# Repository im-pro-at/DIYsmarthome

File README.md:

# DIYsmarthome
Cheap DIY smart home system

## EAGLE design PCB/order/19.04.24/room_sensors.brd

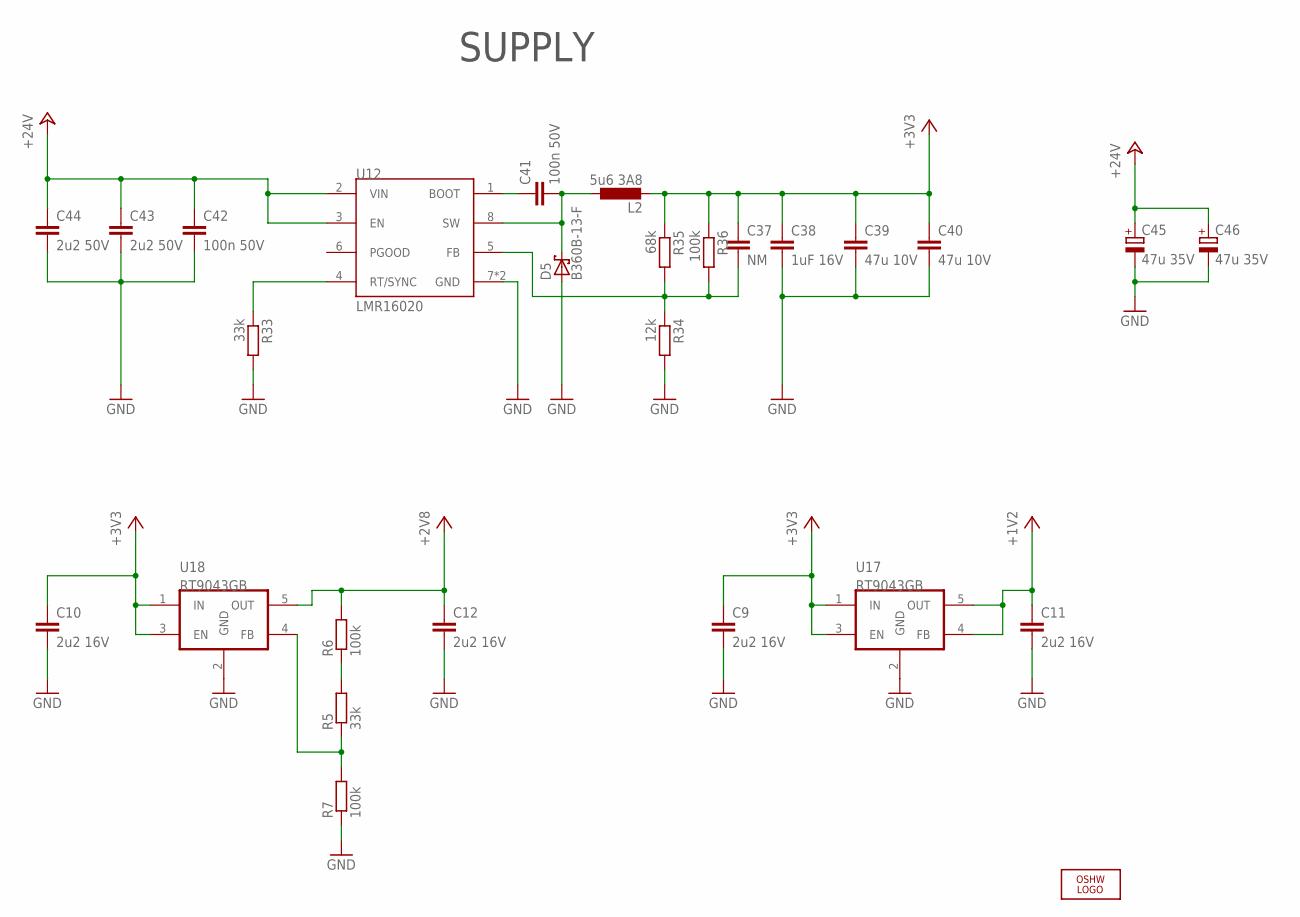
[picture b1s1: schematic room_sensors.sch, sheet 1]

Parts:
C9, C10, C11, C12: 2u2 16V; C1206
C37: NM; C0805
C38: 1uF 16V; C0805
C39, C40: 47u 10V; C1210
C41, C42: 100n 50V; C1206
C43, C44: 2u2 50V; C1206
C45, C46: 47u 35V; UD-5X5,8_NICHICON
D5: B360B-13-F; SMB
L2: 5u6 3A8; SLF10145T-150M2R2-PF
LOGO1: OSHW_LOGO_FILLX0350-NT; OSHW_FILLX350_NOTEXT
R5, R33: 33k; R1206
R6, R7, R36: 100k; R1206
R34: 12k; R1206
R35: 68k; R1206
U12: LMR16020; SOIC127P600X170-8N
U17, U18: RT9043GB; SOP95P275X110-5N

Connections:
+1V2: C11.1, U17.4 (FB), U17.5 (OUT); also elsewhere on the board
+2V8: C12.1, R6.2, U18.5 (OUT); also elsewhere on the board
+3V3: C9.1, C10.1, C37.1, C38.1, C39.1, C40.1, L2.P$2 (2), R35.1, R36.1, U17.1 (IN), U17.3 (EN), U18.1 (IN), U18.3 (EN); also elsewhere on the board
+24V: C42.1, C43.1, C44.1, C45.+, C46.+, U12.2 (VIN), U12.3 (EN); also elsewhere on the board
ESP32_EN1: R5.1, R7.2, U18.4 (FB)
GND: C9.2, C10.2, C11.2, C12.2, C38.2, C39.2, C40.2, C42.2, C43.2, C44.2, C45.-, C46.-, D5.A, R7.1, R33.2, R34.2, U12.7 (GND), U12.9 (GND), U17.2 (GND), U18.2 (GND); also elsewhere on the board
unnamed: R5.2, R6.1
unnamed: R33.1, U12.4 (RT/SYNC)
unnamed: C37.2, R34.1, R35.2, R36.2, U12.5 (FB)
unnamed: C41.2, D5.C, L2.P$1 (1), U12.8 (SW)
unnamed: C41.1, U12.1 (BOOT)

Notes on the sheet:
SUPPLY

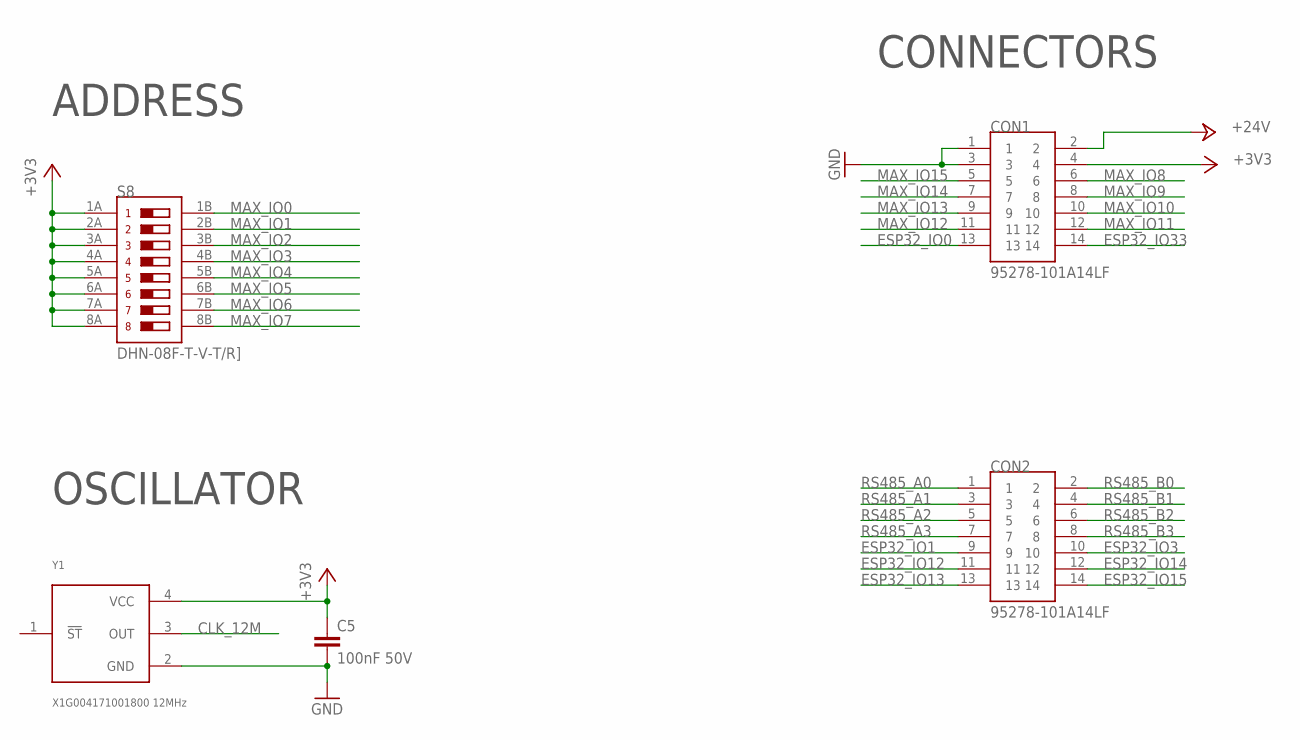
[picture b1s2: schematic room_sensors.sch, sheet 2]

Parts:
C5: 100nF 50V; C0805
CON1, CON2: 95278-101A14LF
S8: DHN-08F-T-V-T/R]
Y1: X1G004171001800 12MHz; OSCCC250X200X80-4N

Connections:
+3V3: C5.1, CON1.4, S8.1A, S8.2A, S8.3A, S8.4A, S8.5A, S8.6A, S8.7A, S8.8A, Y1.4 (VCC); also elsewhere on the board
+24V: CON1.2; also elsewhere on the board
CLK_12M: Y1.3 (OUT); also elsewhere on the board
ESP32_IO0: CON1.13; also elsewhere on the board
ESP32_IO1: CON2.9; also elsewhere on the board
ESP32_IO3: CON2.10; also elsewhere on the board
ESP32_IO12: CON2.11; also elsewhere on the board
ESP32_IO13: CON2.13; also elsewhere on the board
ESP32_IO14: CON2.12; also elsewhere on the board
ESP32_IO15: CON2.14; also elsewhere on the board
ESP32_IO33: CON1.14; also elsewhere on the board
GND: C5.2, CON1.1, CON1.3, Y1.2 (GND); also elsewhere on the board
MAX_IO0: S8.1B; also elsewhere on the board
MAX_IO1: S8.2B; also elsewhere on the board
MAX_IO2: S8.3B; also elsewhere on the board
MAX_IO3: S8.4B; also elsewhere on the board
MAX_IO4: S8.5B; also elsewhere on the board
MAX_IO5: S8.6B; also elsewhere on the board
MAX_IO6: S8.7B; also elsewhere on the board
MAX_IO7: S8.8B; also elsewhere on the board
MAX_IO8: CON1.6; also elsewhere on the board
MAX_IO9: CON1.8; also elsewhere on the board
MAX_IO10: CON1.10; also elsewhere on the board
MAX_IO11: CON1.12; also elsewhere on the board
MAX_IO12: CON1.11; also elsewhere on the board
MAX_IO13: CON1.9; also elsewhere on the board
MAX_IO14: CON1.7; also elsewhere on the board
MAX_IO15: CON1.5; also elsewhere on the board
RS485_A0: CON2.1; also elsewhere on the board
RS485_A1: CON2.3; also elsewhere on the board
RS485_A2: CON2.5; also elsewhere on the board
RS485_A3: CON2.7; also elsewhere on the board
RS485_B0: CON2.2; also elsewhere on the board
RS485_B1: CON2.4; also elsewhere on the board
RS485_B2: CON2.6; also elsewhere on the board
RS485_B3: CON2.8; also elsewhere on the board

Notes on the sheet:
CONNECTORS
ADDRESS
OSCILLATOR

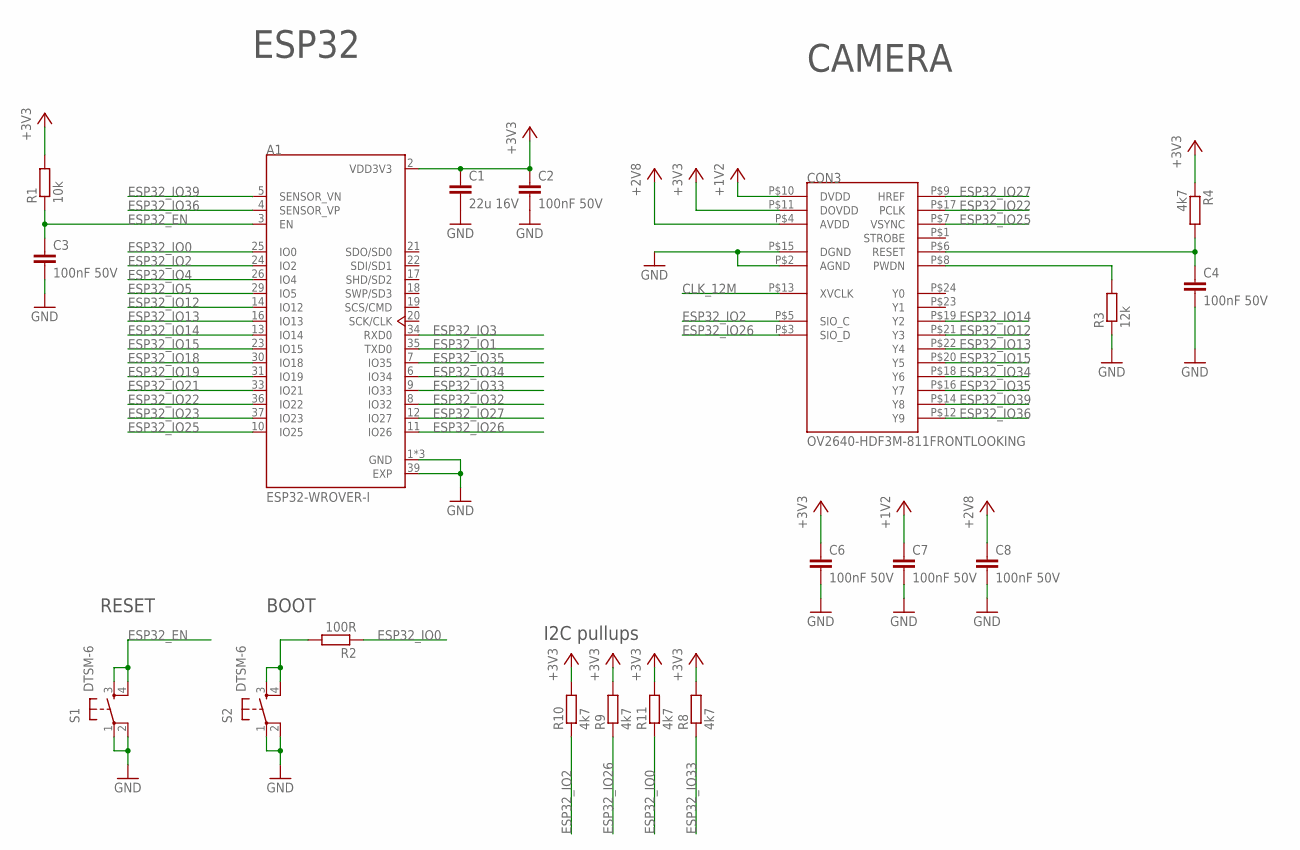
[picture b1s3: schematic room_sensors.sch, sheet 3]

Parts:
A1: ESP32-WROVER-I; XCVR_ESP32-WROVER-I
C1: 22u 16V; C1210
C2, C3, C4, C6, C7, C8: 100nF 50V; C0805
CON3: OV2640-HDF3M-811FRONTLOOKING; FH34SRJ-24S-0.5SH(50)
R1: 10k; R1206
R2: 100R; R1206
R3: 12k; R1206
R4, R8, R9, R10, R11: 4k7; R1206
S1, S2: DTSM-6

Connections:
+1V2: C7.1, CON3.P$10 (DVDD); also elsewhere on the board
+2V8: C8.1, CON3.P$4 (AVDD); also elsewhere on the board
+3V3: A1.2 (VDD3V3), C1.1, C2.1, C6.1, CON3.P$11 (DOVDD), R1.2, R4.1, R8.2, R9.2, R10.2, R11.2; also elsewhere on the board
CLK_12M: CON3.P$13 (XVCLK); also elsewhere on the board
ESP32_BOOT: R2.2, S2.3, S2.4
ESP32_EN: A1.3 (EN), C3.1, R1.1, S1.3, S1.4
ESP32_IO0: A1.25 (IO0), R2.1, R11.1; also elsewhere on the board
ESP32_IO1: A1.35 (TXD0); also elsewhere on the board
ESP32_IO2: A1.24 (IO2), CON3.P$5 (SIO_C), R10.1
ESP32_IO3: A1.34 (RXD0); also elsewhere on the board
ESP32_IO4: A1.26 (IO4); also elsewhere on the board
ESP32_IO5: A1.29 (IO5); also elsewhere on the board
ESP32_IO12: A1.14 (IO12), CON3.P$21 (Y3); also elsewhere on the board
ESP32_IO13: A1.16 (IO13), CON3.P$22 (Y4); also elsewhere on the board
ESP32_IO14: A1.13 (IO14), CON3.P$19 (Y2); also elsewhere on the board
ESP32_IO15: A1.23 (IO15), CON3.P$20 (Y5); also elsewhere on the board
ESP32_IO18: A1.30 (IO18); also elsewhere on the board
ESP32_IO19: A1.31 (IO19); also elsewhere on the board
ESP32_IO21: A1.33 (IO21); also elsewhere on the board
ESP32_IO22: A1.36 (IO22), CON3.P$17 (PCLK)
ESP32_IO23: A1.37 (IO23); also elsewhere on the board
ESP32_IO25: A1.10 (IO25), CON3.P$7 (VSYNC)
ESP32_IO26: A1.11 (IO26), CON3.P$3 (SIO_D), R9.1
ESP32_IO27: A1.12 (IO27), CON3.P$9 (HREF)
ESP32_IO32: A1.8 (IO32); also elsewhere on the board
ESP32_IO33: A1.9 (IO33), R8.1; also elsewhere on the board
ESP32_IO34: A1.6 (IO34), CON3.P$18 (Y6)
ESP32_IO35: A1.7 (IO35), CON3.P$16 (Y7)
ESP32_IO36: A1.4 (SENSOR_VP), CON3.P$12 (Y9)
ESP32_IO39: A1.5 (SENSOR_VN), CON3.P$14 (Y8)
GND: A1.1 (GND), A1.15 (GND), A1.38 (GND), A1.39 (EXP), C1.2, C2.2, C3.2, C4.2, C6.2, C7.2, C8.2, CON3.P$2 (AGND), CON3.P$15 (DGND), R3.1, S1.1, S1.2, S2.1, S2.2; also elsewhere on the board
unnamed: CON3.P$8 (PWDN), R3.2
unnamed: C4.1, CON3.P$6 (RESET), R4.2

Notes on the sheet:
RESET
BOOT
ESP32
CAMERA
I2C pullups

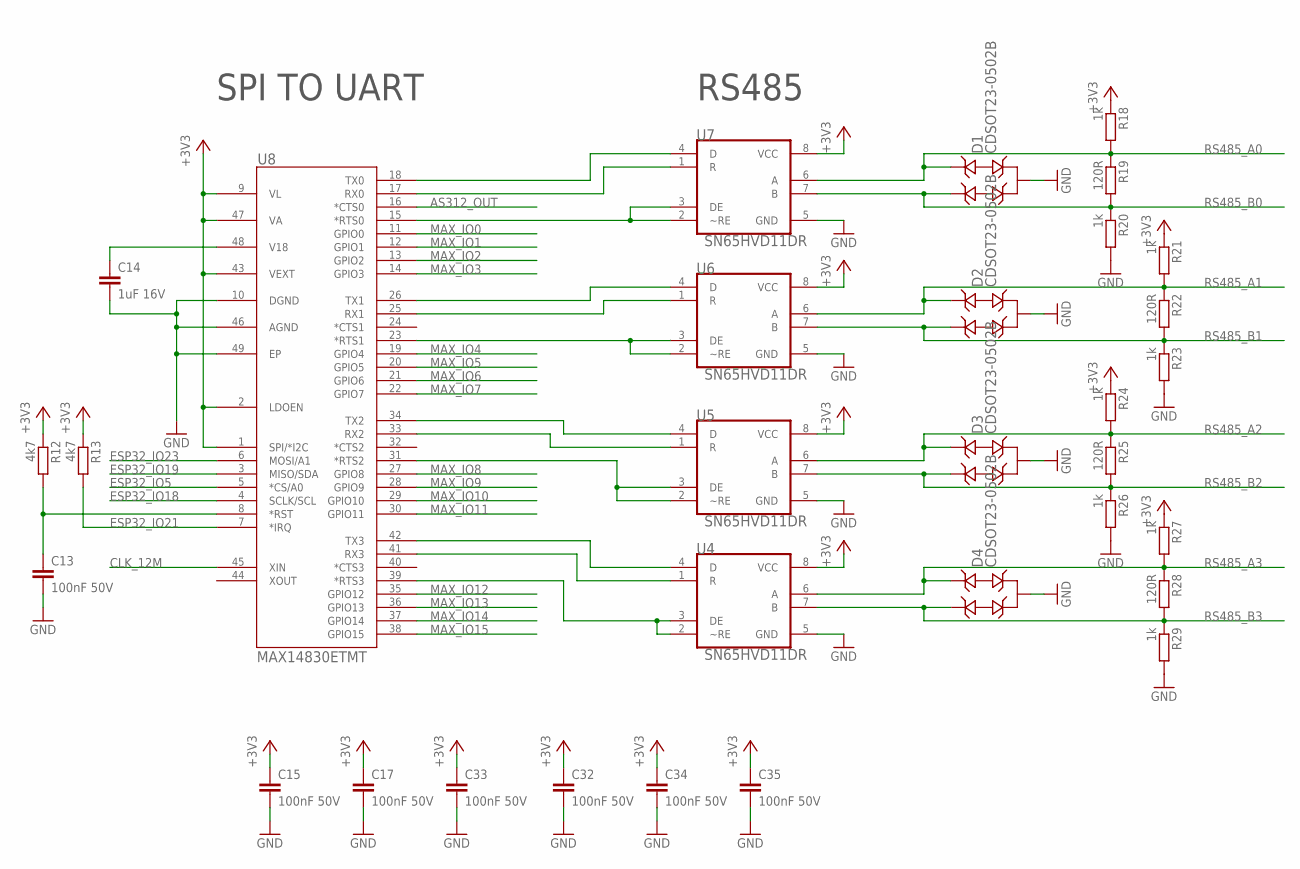
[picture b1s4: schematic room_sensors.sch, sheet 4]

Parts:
C13, C15, C17, C32, C33, C34, C35: 100nF 50V; C0805
C14: 1uF 16V; C0805
D1, D2, D3, D4: CDSOT23-0502B; SOT-23-3
R12, R13: 4k7; R1206
R18, R20, R21, R23, R24, R26, R27, R29: 1k; R1206
R19, R22, R25, R28: 120R; R1206
U4, U5, U6, U7: SN65HVD11DR; SOIC127P600X175-8N
U8: MAX14830ETMT; 21-0144H_T4877-3

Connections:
+3V3: C15.1, C17.1, C32.1, C33.1, C34.1, C35.1, R12.1, R13.1, R18.1, R21.1, R24.1, R27.1, U4.8 (VCC), U5.8 (VCC), U6.8 (VCC), U7.8 (VCC), U8.1 (SPI/*I2C), U8.2 (LDOEN), U8.9 (VL), U8.43 (VEXT), U8.47 (VA); also elsewhere on the board
AS312_OUT: U8.16 (*CTS0); also elsewhere on the board
CLK_12M: U8.45 (XIN); also elsewhere on the board
ESP32_IO5: U8.5 (*CS/A0); also elsewhere on the board
ESP32_IO18: U8.4 (SCLK/SCL); also elsewhere on the board
ESP32_IO19: U8.3 (MISO/SDA); also elsewhere on the board
ESP32_IO21: R13.2, U8.7 (*IRQ); also elsewhere on the board
ESP32_IO23: U8.6 (MOSI/A1); also elsewhere on the board
GND: C13.2, C14.2, C15.2, C17.2, C32.2, C33.2, C34.2, C35.2, D1.3 (GND), D2.3 (GND), D3.3 (GND), D4.3 (GND), R20.2, R23.2, R26.2, R29.2, U4.5 (GND), U5.5 (GND), U6.5 (GND), U7.5 (GND), U8.10 (DGND), U8.46 (AGND), U8.49 (EP); also elsewhere on the board
MAX_IO0: U8.11 (GPIO0); also elsewhere on the board
MAX_IO1: U8.12 (GPIO1); also elsewhere on the board
MAX_IO2: U8.13 (GPIO2); also elsewhere on the board
MAX_IO3: U8.14 (GPIO3); also elsewhere on the board
MAX_IO4: U8.19 (GPIO4); also elsewhere on the board
MAX_IO5: U8.20 (GPIO5); also elsewhere on the board
MAX_IO6: U8.21 (GPIO6); also elsewhere on the board
MAX_IO7: U8.22 (GPIO7); also elsewhere on the board
MAX_IO8: U8.27 (GPIO8); also elsewhere on the board
MAX_IO9: U8.28 (GPIO9); also elsewhere on the board
MAX_IO10: U8.29 (GPIO10); also elsewhere on the board
MAX_IO11: U8.30 (GPIO11); also elsewhere on the board
MAX_IO12: U8.35 (GPIO12); also elsewhere on the board
MAX_IO13: U8.36 (GPIO13); also elsewhere on the board
MAX_IO14: U8.37 (GPIO14); also elsewhere on the board
MAX_IO15: U8.38 (GPIO15); also elsewhere on the board
unnamed: U7.4 (D), U8.18 (TX0)
unnamed: U7.1 (R), U8.17 (RX0)
unnamed: U6.4 (D), U8.26 (TX1)
unnamed: U6.1 (R), U8.25 (RX1)
unnamed: U5.4 (D), U8.34 (TX2)
unnamed: U5.1 (R), U8.33 (RX2)
unnamed: U4.4 (D), U8.42 (TX3)
unnamed: U4.1 (R), U8.41 (RX3)
unnamed: U7.2 (~RE), U7.3 (DE), U8.15 (*RTS0)
unnamed: U6.2 (~RE), U6.3 (DE), U8.23 (*RTS1)
unnamed: C13.1, R12.2, U8.8 (*RST)
unnamed: U5.2 (~RE), U5.3 (DE), U8.31 (*RTS2)
unnamed: U4.2 (~RE), U4.3 (DE), U8.39 (*RTS3)
unnamed: C14.1, U8.48 (V18)
RS485_A0: D1.2 (IO2), R18.2, R19.1, U7.6 (A); also elsewhere on the board
RS485_A1: D2.2 (IO2), R21.2, R22.1, U6.6 (A); also elsewhere on the board
RS485_A2: D3.2 (IO2), R24.2, R25.1, U5.6 (A); also elsewhere on the board
RS485_A3: D4.2 (IO2), R27.2, R28.1, U4.6 (A); also elsewhere on the board
RS485_B0: D1.1 (IO1), R19.2, R20.1, U7.7 (B); also elsewhere on the board
RS485_B1: D2.1 (IO1), R22.2, R23.1, U6.7 (B); also elsewhere on the board
RS485_B2: D3.1 (IO1), R25.2, R26.1, U5.7 (B); also elsewhere on the board
RS485_B3: D4.1 (IO1), R28.2, R29.1, U4.7 (B); also elsewhere on the board

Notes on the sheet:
SPI TO UART
RS485

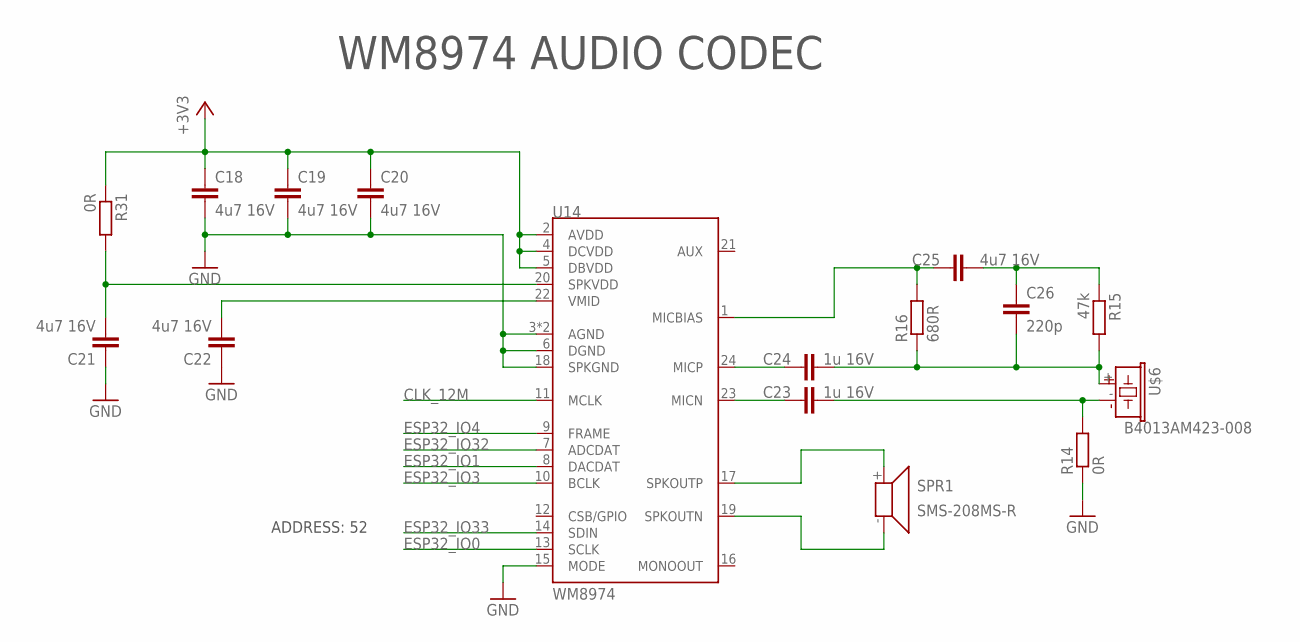
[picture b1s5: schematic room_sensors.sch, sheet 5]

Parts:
C18, C19, C20, C21, C22, C25: 4u7 16V; C0805
C23, C24: 1u 16V; C0805
C26: 220p; C0805
R14: 0R; R1206
R15: 47k; R1206
R16: 680R; R1206
R31: 0R; R0603
SPR1: SMS-208MS-R; SMS-2008MS-R
U14: WM8974; QFN-24_ALT2
U$6: B4013AM423-008; MIC

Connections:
+3V3: C18.1, C19.1, C20.1, R31.1, U14.2 (AVDD), U14.4 (DCVDD), U14.5 (DBVDD); also elsewhere on the board
CLK_12M: U14.11 (MCLK); also elsewhere on the board
ESP32_IO0: U14.13 (SCLK); also elsewhere on the board
ESP32_IO1: U14.8 (DACDAT); also elsewhere on the board
ESP32_IO3: U14.10 (BCLK); also elsewhere on the board
ESP32_IO4: U14.9 (FRAME); also elsewhere on the board
ESP32_IO32: U14.7 (ADCDAT); also elsewhere on the board
ESP32_IO33: U14.14 (SDIN); also elsewhere on the board
GND: C18.2, C19.2, C20.2, C21.1, C22.1, R14.1, U14.3 (AGND), U14.6 (DGND), U14.15 (MODE), U14.18 (SPKGND), U14.EP (AGND); also elsewhere on the board
unnamed: C22.2, U14.22 (VMID)
unnamed: SPR1.+ (1), U14.17 (SPKOUTP)
unnamed: SPR1.- (2), U14.19 (SPKOUTN)
unnamed: C23.2, R14.2, U$6.-
unnamed: C24.2, C26.2, R15.2, R16.1, U$6.+
unnamed: C23.1, U14.23 (MICN)
unnamed: C24.1, U14.24 (MICP)
unnamed: C25.1, R16.2, U14.1 (MICBIAS)
unnamed: C25.2, C26.1, R15.1
unnamed: C21.2, R31.2, U14.20 (SPKVDD)

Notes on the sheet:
WM8974 AUDIO CODEC
ADDRESS: 52

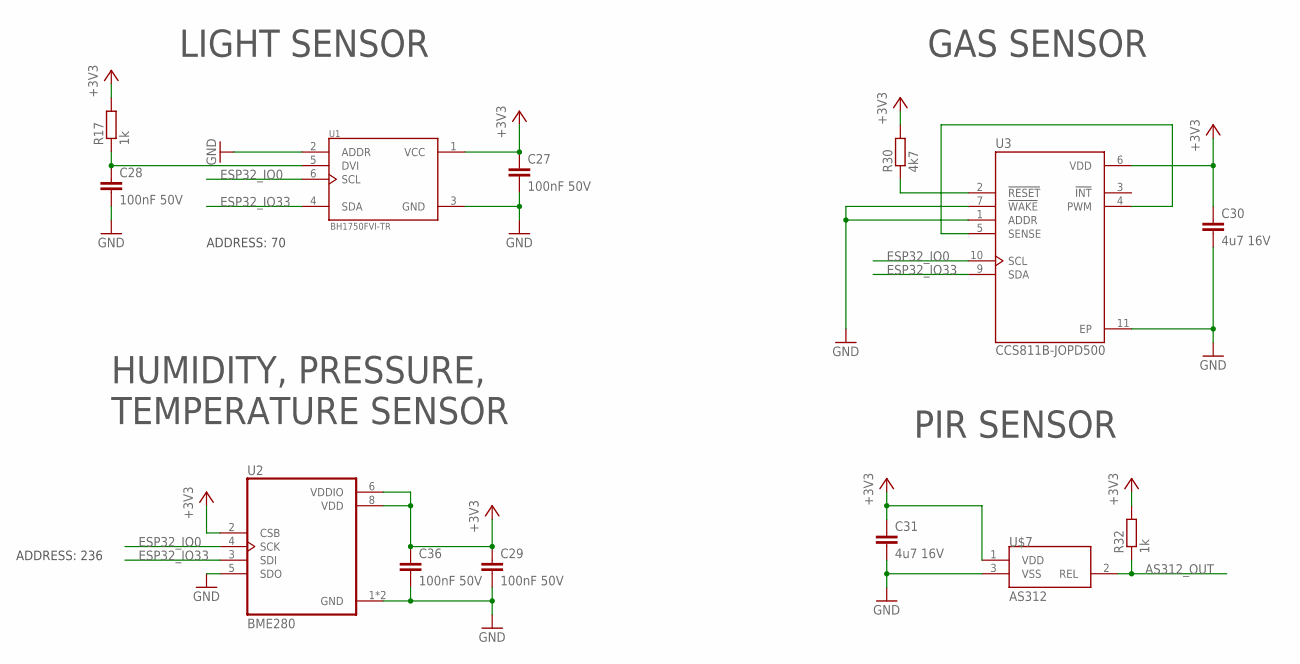
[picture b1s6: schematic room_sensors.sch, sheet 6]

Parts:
C27, C28, C29, C36: 100nF 50V; C0805
C30, C31: 4u7 16V; C0805
R17, R32: 1k; R1206
R30: 4k7; R1206
U1: BH1750FVI-TR; SOTFL50P300X75-6N
U2: BME280; PSON65P250X250X100-8N
U3: CCS811B-JOPD500; SON60P400X270X110-11N
U$7: AS312; TO-39

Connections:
+3V3: C27.1, C29.1, C30.1, C31.1, C36.1, R17.2, R30.2, R32.2, U1.1 (VCC), U2.2 (CSB), U2.6 (VDDIO), U2.8 (VDD), U3.6 (VDD), U$7.1 (VDD); also elsewhere on the board
AS312_OUT: R32.1, U$7.2 (REL); also elsewhere on the board
ESP32_IO0: U1.6 (SCL), U2.4 (SCK), U3.10 (SCL); also elsewhere on the board
ESP32_IO33: U1.4 (SDA), U2.3 (SDI), U3.9 (SDA); also elsewhere on the board
GND: C27.2, C28.2, C29.2, C30.2, C31.2, C36.2, U1.2 (ADDR), U1.3 (GND), U2.1 (GND), U2.5 (SDO), U2.7 (GND), U3.1 (ADDR), U3.7 (!WAKE), U3.11 (EP), U$7.3 (VSS); also elsewhere on the board
unnamed: C28.1, R17.1, U1.5 (DVI)
unnamed: U3.4 (PWM), U3.5 (SENSE)
unnamed: R30.1, U3.2 (!RESET)

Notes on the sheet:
LIGHT SENSOR
ADDRESS: 70
HUMIDITY, PRESSURE, TEMPERATURE SENSOR
ADDRESS: 236
GAS SENSOR
PIR SENSOR

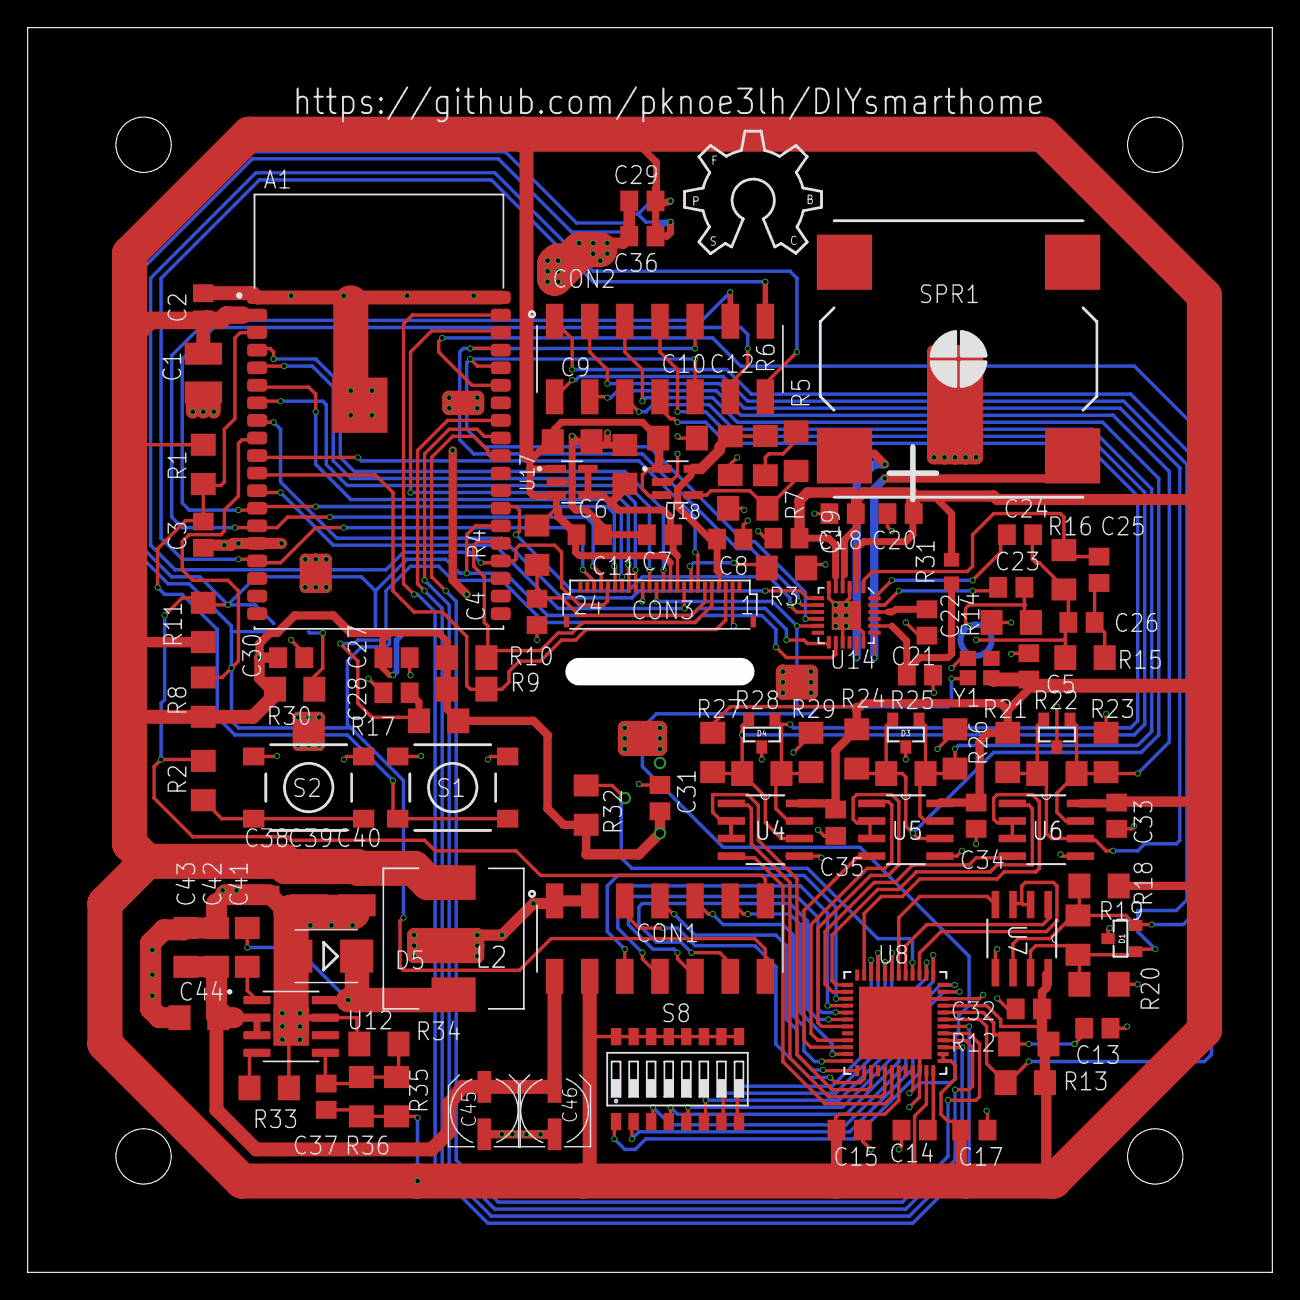
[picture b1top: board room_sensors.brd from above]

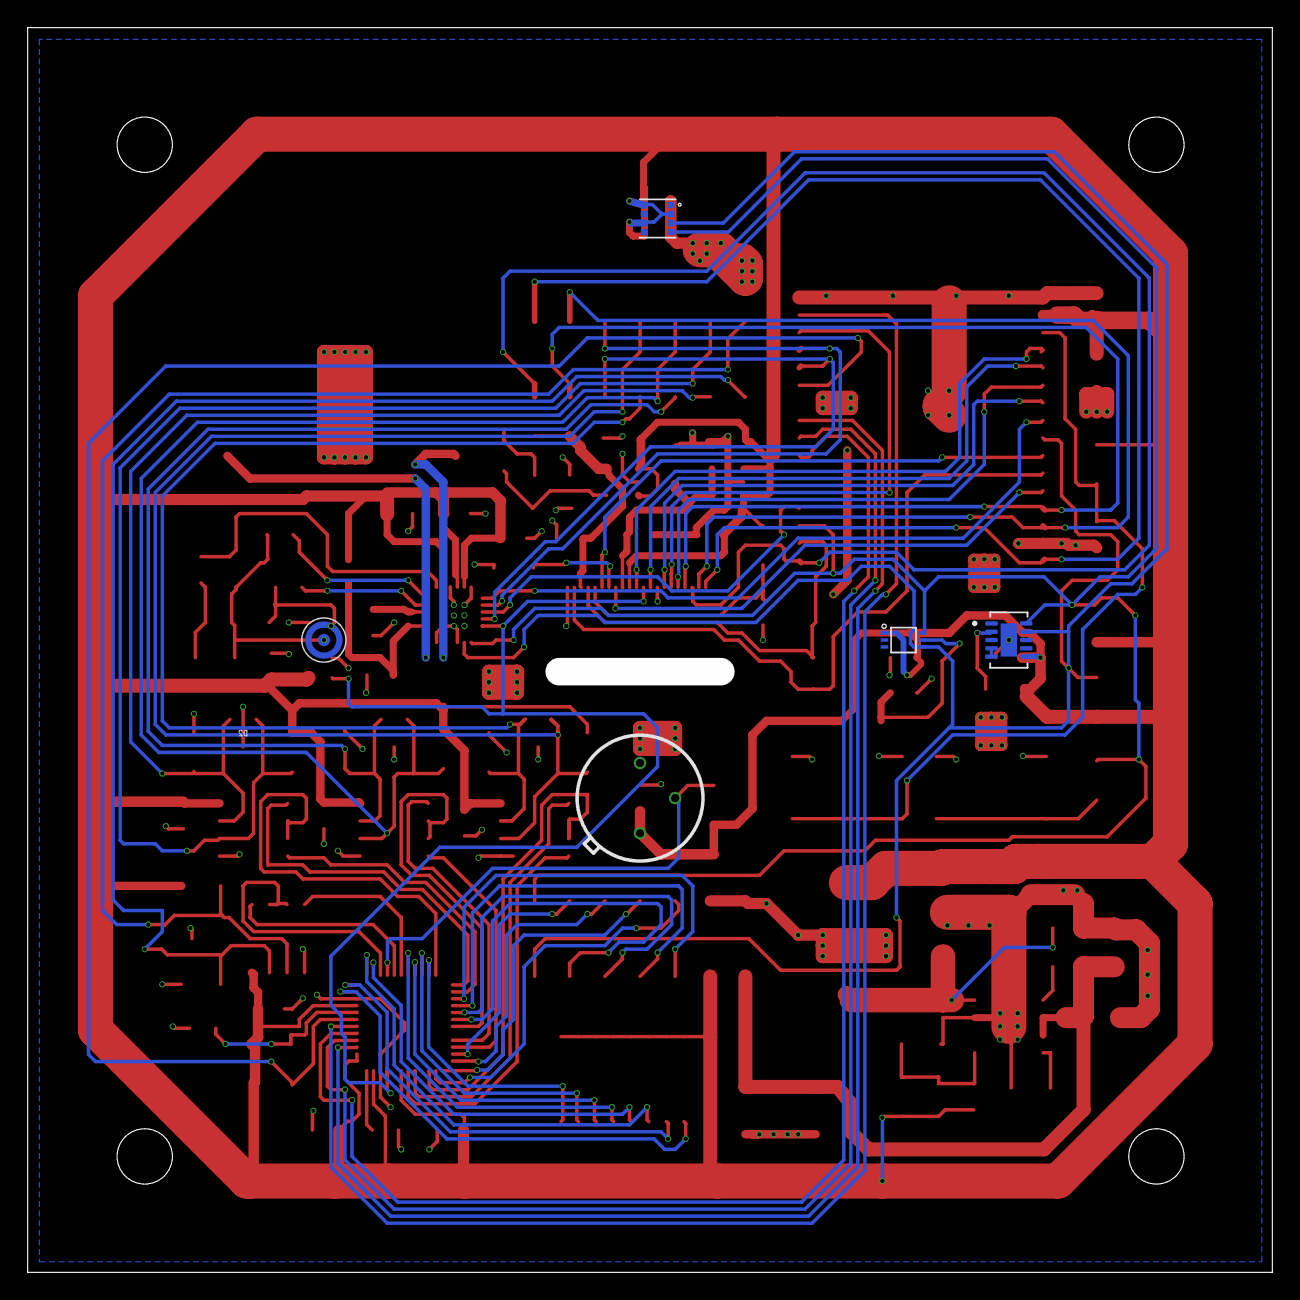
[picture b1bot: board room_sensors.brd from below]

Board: 2 copper layers, 90.0 x 90.0 mm, 111 parts (5 on the bottom side), 92 nets.

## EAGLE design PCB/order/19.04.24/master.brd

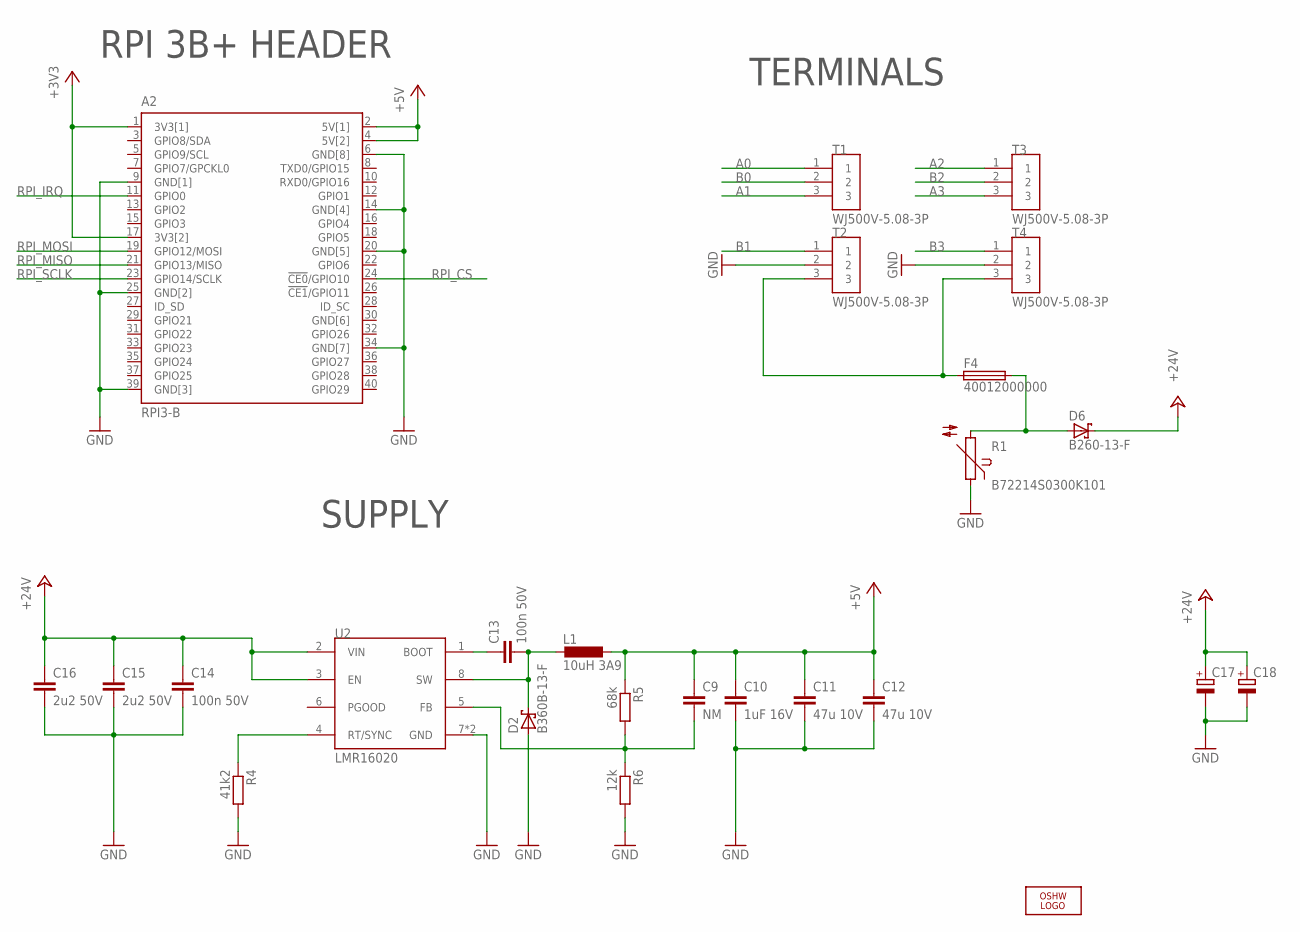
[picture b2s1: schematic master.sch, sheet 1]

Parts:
A2: RPI3-B
C9: NM; C0805
C10: 1uF 16V; C0805
C11, C12: 47u 10V; C1210
C13, C14: 100n 50V; C1206
C15, C16: 2u2 50V; C1206
C17, C18: CPOL-EUUD-5X5,8; UD-5X5,8_NICHICON
D2: B360B-13-F; SMB
D6: B260-13-F; SMB
F4: 40012000000; 400
L1: 10uH 3A9; 1217AS
LOGO1: OSHW_LOGO_FILLX0350-NT; OSHW_FILLX350_NOTEXT
R1: B72214S0300K101; S14K300
R4: 41k2; R1206
R5: 68k; R1206
R6: 12k; R1206
T1, T2, T3, T4: WJ500V-5.08-3P
U2: LMR16020; SOIC127P600X170-8N

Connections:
+3V3: A2.1 (3V3[1]), A2.17 (3V3[2]); also elsewhere on the board
+5V: A2.2 (5V[1]), A2.4 (5V[2]), C9.1, C10.1, C11.1, C12.1, L1.1, R5.1
+24V: C14.1, C15.1, C16.1, C17.+, C18.+, D6.C, U2.2 (VIN), U2.3 (EN)
A0: T1.1; also elsewhere on the board
A1: T1.3; also elsewhere on the board
A2: T3.1; also elsewhere on the board
A3: T3.3; also elsewhere on the board
B0: T1.2; also elsewhere on the board
B1: T2.1; also elsewhere on the board
B2: T3.2; also elsewhere on the board
B3: T4.1; also elsewhere on the board
GND: A2.6 (GND[8]), A2.9 (GND[1]), A2.14 (GND[4]), A2.20 (GND[5]), A2.25 (GND[2]), A2.34 (GND[7]), A2.39 (GND[3]), C10.2, C11.2, C12.2, C14.2, C15.2, C16.2, C17.-, C18.-, D2.A, R1.1, R4.2, R6.2, T2.2, T4.2, U2.7 (GND), U2.9 (GND); also elsewhere on the board
GND[6]: A2.30 (GND[6])
unnamed: R4.1, U2.4 (RT/SYNC)
unnamed: C9.2, R5.2, R6.1, U2.5 (FB)
unnamed: C13.2, D2.C, L1.2, U2.8 (SW)
unnamed: C13.1, U2.1 (BOOT)
unnamed: F4.P$1 (1), T2.3, T4.3
unnamed: D6.A, F4.P$2 (2), R1.2
RPI_CS: A2.24 (!CE0!/GPIO10); also elsewhere on the board
RPI_IRQ: A2.11 (GPIO0); also elsewhere on the board
RPI_MISO: A2.21 (GPIO13/MISO); also elsewhere on the board
RPI_MOSI: A2.19 (GPIO12/MOSI); also elsewhere on the board
RPI_SCLK: A2.23 (GPIO14/SCLK); also elsewhere on the board

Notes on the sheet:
SUPPLY
RPI 3B+ HEADER
TERMINALS

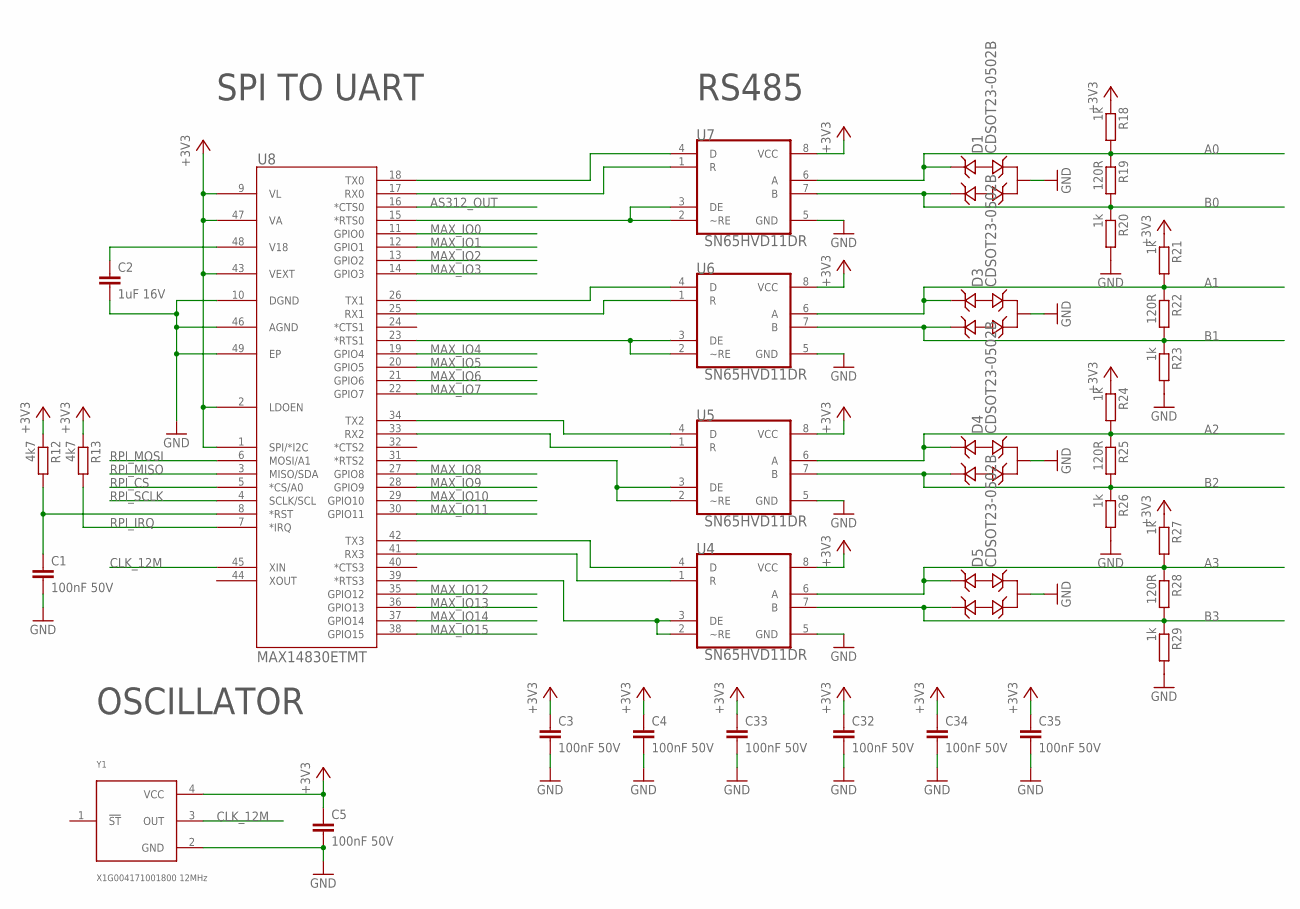
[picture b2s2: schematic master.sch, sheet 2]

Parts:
C1, C3, C4, C5, C32, C33, C34, C35: 100nF 50V; C0805
C2: 1uF 16V; C0805
D1, D3, D4, D5: CDSOT23-0502B; SOT-23-3
R12, R13: 4k7; R1206
R18, R20, R21, R23, R24, R26, R27, R29: 1k; R1206
R19, R22, R25, R28: 120R; R1206
U4, U5, U6, U7: SN65HVD11DR; SOIC127P600X175-8N
U8: MAX14830ETMT; 21-0144H_T4877-3
Y1: X1G004171001800 12MHz; OSCCC250X200X80-4N

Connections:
+3V3: C3.1, C4.1, C5.1, C32.1, C33.1, C34.1, C35.1, R12.1, R13.1, R18.1, R21.1, R24.1, R27.1, U4.8 (VCC), U5.8 (VCC), U6.8 (VCC), U7.8 (VCC), U8.1 (SPI/*I2C), U8.2 (LDOEN), U8.9 (VL), U8.43 (VEXT), U8.47 (VA), Y1.4 (VCC); also elsewhere on the board
A0: D1.2 (IO2), R18.2, R19.1, U7.6 (A); also elsewhere on the board
A1: D3.2 (IO2), R21.2, R22.1, U6.6 (A); also elsewhere on the board
A2: D4.2 (IO2), R24.2, R25.1, U5.6 (A); also elsewhere on the board
A3: D5.2 (IO2), R27.2, R28.1, U4.6 (A); also elsewhere on the board
AS312_OUT: U8.16 (*CTS0)
B0: D1.1 (IO1), R19.2, R20.1, U7.7 (B); also elsewhere on the board
B1: D3.1 (IO1), R22.2, R23.1, U6.7 (B); also elsewhere on the board
B2: D4.1 (IO1), R25.2, R26.1, U5.7 (B); also elsewhere on the board
B3: D5.1 (IO1), R28.2, R29.1, U4.7 (B); also elsewhere on the board
CLK_12M: U8.45 (XIN), Y1.3 (OUT)
GND: C1.2, C2.2, C3.2, C4.2, C5.2, C32.2, C33.2, C34.2, C35.2, D1.3 (GND), D3.3 (GND), D4.3 (GND), D5.3 (GND), R20.2, R23.2, R26.2, R29.2, U4.5 (GND), U5.5 (GND), U6.5 (GND), U7.5 (GND), U8.10 (DGND), U8.46 (AGND), U8.49 (EP), Y1.2 (GND); also elsewhere on the board
MAX_IO0: U8.11 (GPIO0)
MAX_IO1: U8.12 (GPIO1)
MAX_IO2: U8.13 (GPIO2)
MAX_IO3: U8.14 (GPIO3)
MAX_IO4: U8.19 (GPIO4)
MAX_IO5: U8.20 (GPIO5)
MAX_IO6: U8.21 (GPIO6)
MAX_IO7: U8.22 (GPIO7)
MAX_IO8: U8.27 (GPIO8)
MAX_IO9: U8.28 (GPIO9)
MAX_IO10: U8.29 (GPIO10)
MAX_IO11: U8.30 (GPIO11)
MAX_IO12: U8.35 (GPIO12)
MAX_IO13: U8.36 (GPIO13)
MAX_IO14: U8.37 (GPIO14)
MAX_IO15: U8.38 (GPIO15)
unnamed: U6.1 (R), U8.25 (RX1)
unnamed: U5.4 (D), U8.34 (TX2)
unnamed: U7.4 (D), U8.18 (TX0)
unnamed: U5.1 (R), U8.33 (RX2)
unnamed: U7.1 (R), U8.17 (RX0)
unnamed: U6.4 (D), U8.26 (TX1)
unnamed: U4.4 (D), U8.42 (TX3)
unnamed: U4.1 (R), U8.41 (RX3)
unnamed: U7.2 (~RE), U7.3 (DE), U8.15 (*RTS0)
unnamed: U6.2 (~RE), U6.3 (DE), U8.23 (*RTS1)
unnamed: U5.2 (~RE), U5.3 (DE), U8.31 (*RTS2)
unnamed: U4.2 (~RE), U4.3 (DE), U8.39 (*RTS3)
unnamed: C1.1, R12.2, U8.8 (*RST)
unnamed: C2.1, U8.48 (V18)
RPI_CS: U8.5 (*CS/A0); also elsewhere on the board
RPI_IRQ: R13.2, U8.7 (*IRQ); also elsewhere on the board
RPI_MISO: U8.3 (MISO/SDA); also elsewhere on the board
RPI_MOSI: U8.6 (MOSI/A1); also elsewhere on the board
RPI_SCLK: U8.4 (SCLK/SCL); also elsewhere on the board

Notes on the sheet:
SPI TO UART
RS485
OSCILLATOR

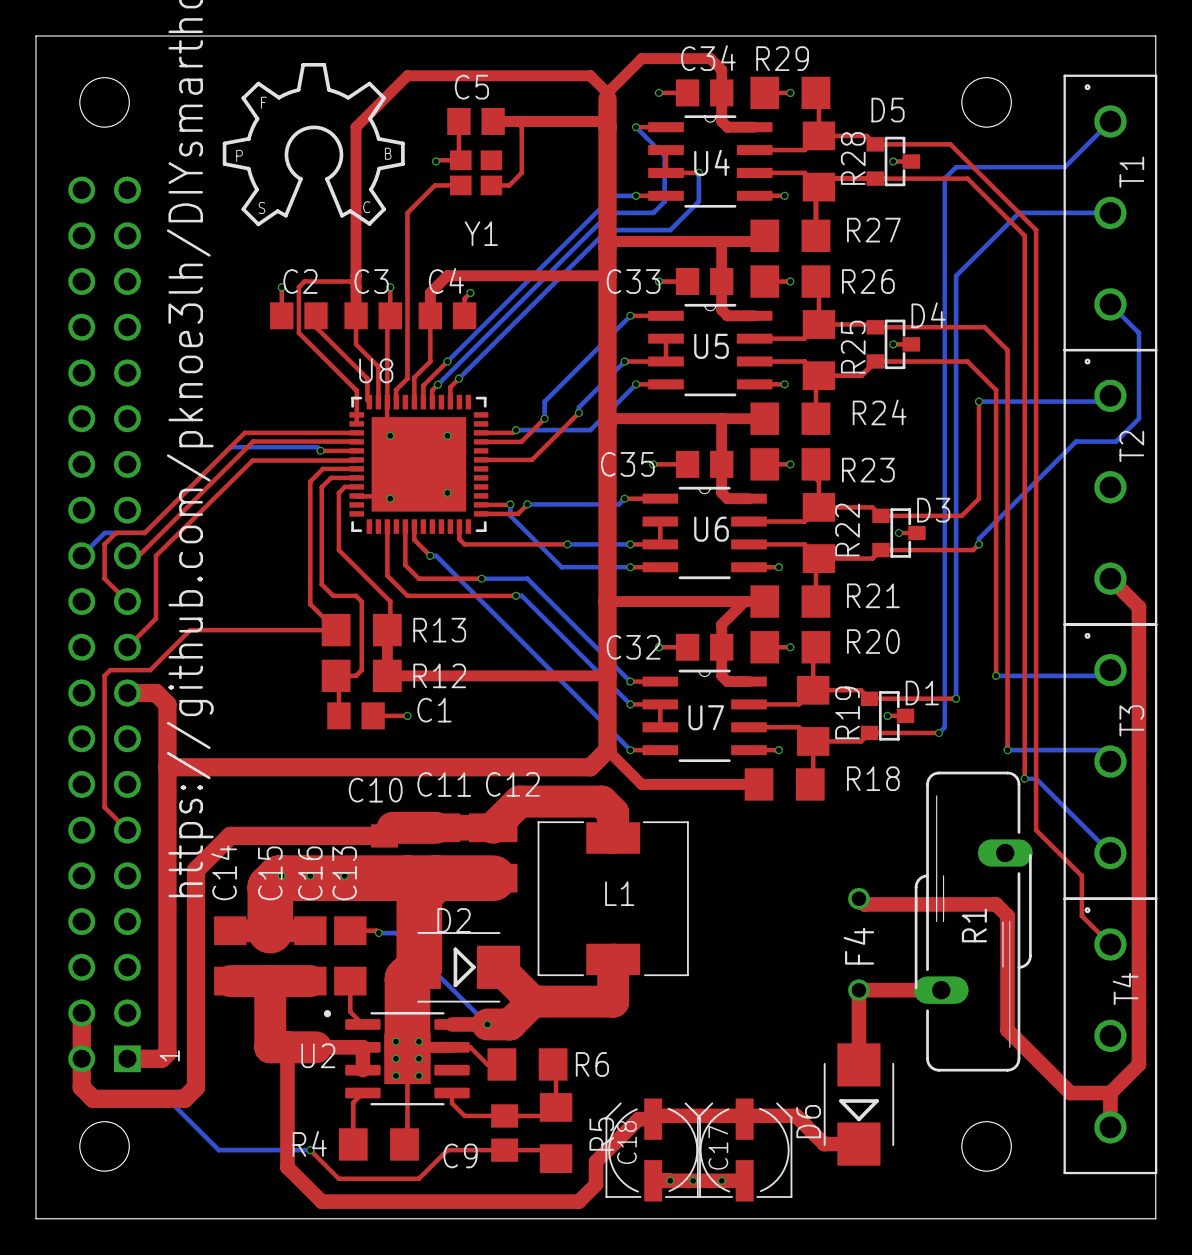
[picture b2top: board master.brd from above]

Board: 2 copper layers, 62.2 x 65.7 mm, 58 parts (0 on the bottom side), 38 nets.
